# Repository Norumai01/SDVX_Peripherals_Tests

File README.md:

# controller_subtests

Breadboard prototyping tests for a custom Sound Voltex (SDVX) controller built on the Raspberry Pi Pico 2 H (RP2350).

Each subfolder is a self-contained test with its own `CMakeLists.txt` and `main.c`.

---

## Project Structure

```
controller_subtests/
├── CMakeLists.txt          ← top-level, registers all subtests
├── pico_sdk_import.cmake
├── serial_monitor.py       ← Python serial monitor for debugging
├── mx_switch_test/
│   ├── CMakeLists.txt
│   └── main.c              ← Cherry MX Brown button + onboard LED test
└── encoder_test/
    ├── CMakeLists.txt
    └── main.c              ← Bourns PEC11R rotary encoder test
```

---

## Hardware

| Component | Part |
|---|---|
| Microcontroller | Raspberry Pi Pico 2 H (RP2350, pre-soldered headers) |
| Buttons | Cherry MX Brown switches (jumper wires soldered directly to pins) |
| Encoders | Bourns PEC11R-xxxxK (no detents, with push switch) |

---

## Subtest: mx_switch_test

Tests a single Cherry MX Brown switch on GPIO 0. Jumper wires are soldered directly to the two switch pins. Toggles the onboard LED on press/release and prints state over USB serial.

**Wiring:**
```
Switch Pin 1  → GPIO 0  (pin 1)
Switch Pin 2  → GND
```

> **Note:** Uses the Pico's internal pull-up — no external resistor needed. Pin reads HIGH at rest and LOW when pressed.

---

## Subtest: encoder_test

Tests a Bourns PEC11R rotary encoder — quadrature rotation via interrupt and push switch via polling.

**Wiring:**
```
ENC A    → GPIO 10  (pin 14)
ENC C    → GND
ENC B    → GPIO 11  (pin 15)
SW pin 1 → GPIO 12  (pin 16)
SW pin 2 → GND
```

**How it works:**
- An interrupt fires on every rising/falling edge of channel A
- Inside the ISR, A and B are compared — if they differ, direction is CW (+1), if same, direction is CCW (-1)
- The push switch is polled in the main loop with debounce

---

## Building

Requires the [Raspberry Pi Pico SDK](https://github.com/raspberrypi/pico-sdk). Set `PICO_SDK_PATH` in your environment or let CLion handle it via the CMake Environment field.

```bash
mkdir cmake-build-debug && cd cmake-build-debug
cmake ..
make
```

Each subtest outputs its own `.uf2` into its own subfolder:
```
cmake-build-debug/
├── mx_switch_test/
│   └── mx_switch_test.uf2
└── encoder_test/
    └── encoder_test.uf2
```

**To flash:**
1. Hold BOOTSEL on the Pico while plugging in USB
2. It mounts as a drive called `RP2350`
3. Drag and drop the `.uf2` onto the `RP2350` drive

---

## Serial Monitor

Use the included `serial_monitor.py` to watch output over USB serial.

**Requirements:**
```bash
pip install pyserial
```

**Run:**
```bash
python serial_monitor.py
```

Defaults to `COM3` at `115200` baud. Edit `PORT` at the top of the script if your Pico is on a different port (check Device Manager → Ports (COM & LPT)).

## CLion Serial Monitor (alternative)

CLion has a built-in serial monitor under **Tools → Serial Monitor**.

Settings that must be enabled for it to work with the Pico:
- **Enable HW Flow Control** — on
- **Local Echo** — on
- **DTR** — enabled (this is what actually triggers the Pico to send output)

Without DTR enabled, the monitor connects but receives nothing.

---

## Notes

- Both encoder A and B pins use the Pico's internal pull-ups — no external resistors needed for basic testing
- For final PCB design, add a hardware filter (10KΩ + 0.01µF on each channel) per the PEC11R datasheet recommendation to reduce contact bounce at higher RPM
- The encoder's position counter is unbounded (`volatile int`) — for HID use, report the delta each frame rather than an absolute value

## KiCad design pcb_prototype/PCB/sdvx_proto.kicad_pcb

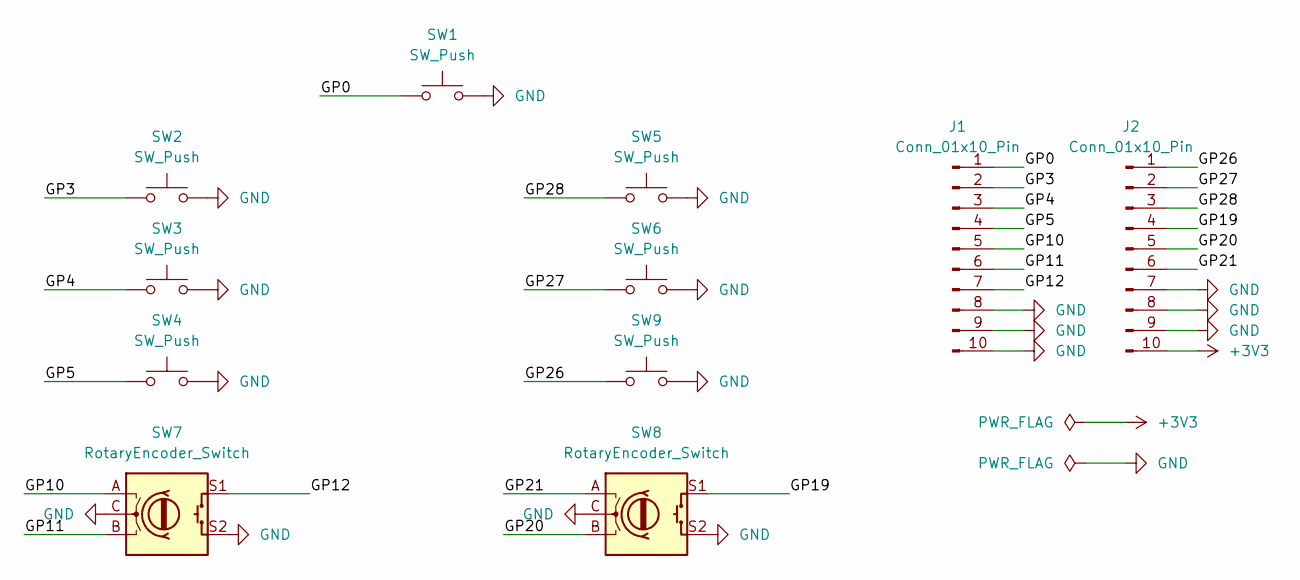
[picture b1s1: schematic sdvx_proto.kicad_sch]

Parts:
J1, J2: Conn_01x10_Pin; PinHeader_1x10_P2.54mm_Vertical
SW1, SW2, SW3, SW4, SW5, SW6, SW9: SW_Push; MX-Solderable-1U
SW7, SW8: RotaryEncoder_Switch; RotaryEncoder_Alps_EC11E-Switch_Vertical_H20mm

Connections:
+3V3: J2.10
/GP0: J1.1, SW1.1
/GP3: J1.2, SW2.1
/GP4: J1.3, SW3.1
/GP5: J1.4, SW4.1
/GP10: J1.5, SW7.A
/GP11: J1.6, SW7.B
/GP12: J1.7, SW7.S1
/GP19: J2.4, SW8.S1
/GP20: J2.5, SW8.B
/GP21: J2.6, SW8.A
/GP26: J2.1, SW9.1
/GP27: J2.2, SW6.1
/GP28: J2.3, SW5.1
GND: J1.8, J1.9, J1.10, J2.7, J2.8, J2.9, SW1.2, SW2.2, SW3.2, SW4.2, SW5.2, SW6.2, SW7.C, SW7.S2, SW8.C, SW8.S2, SW9.2

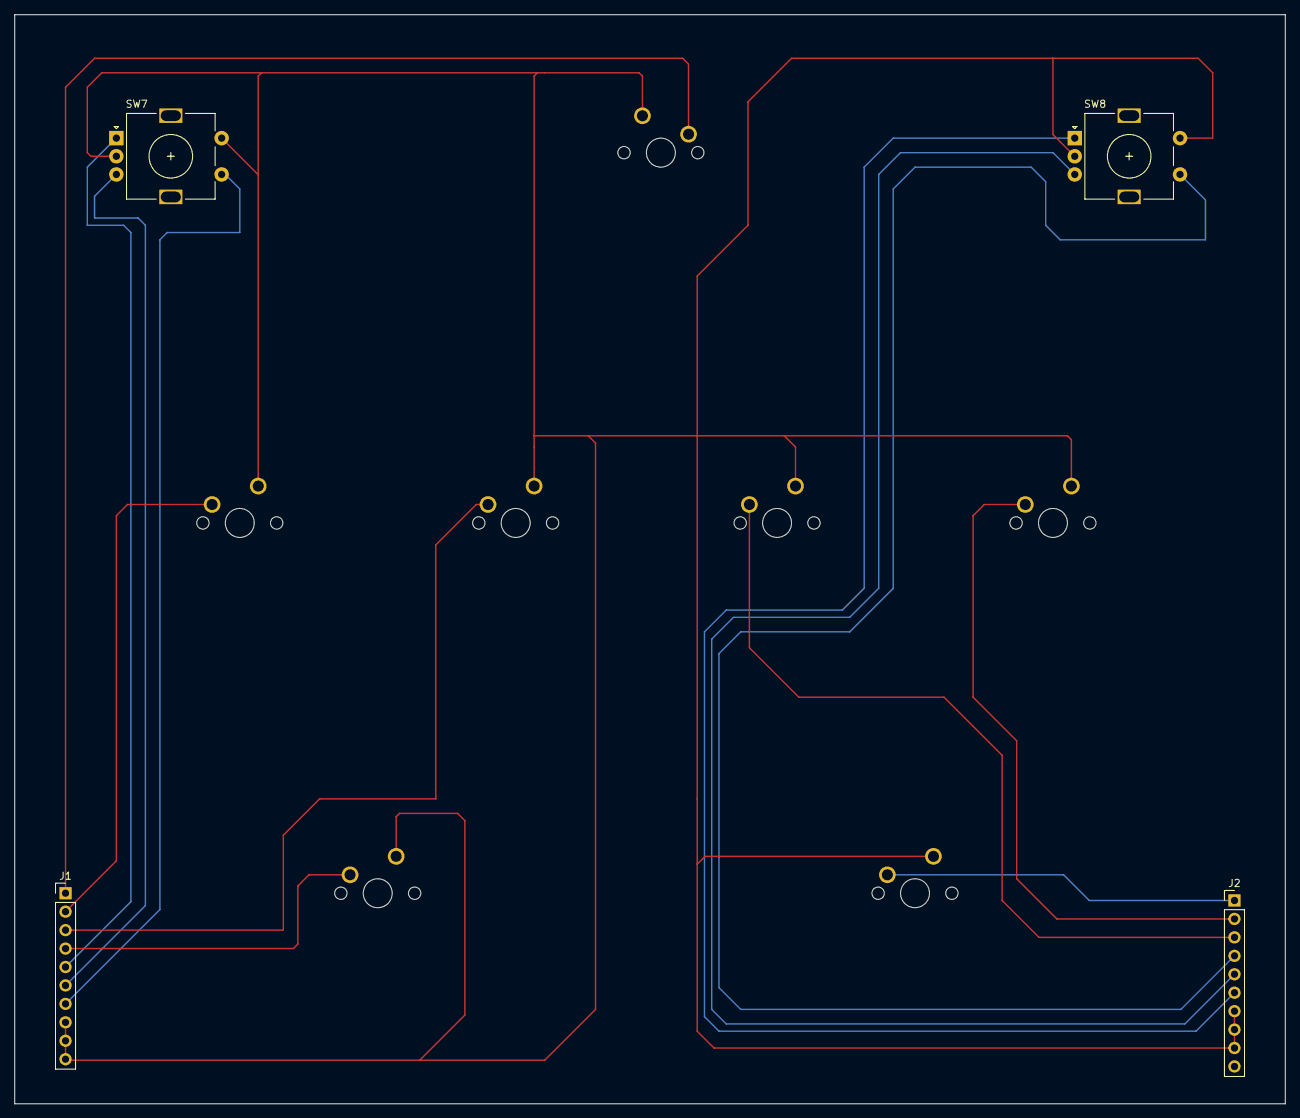
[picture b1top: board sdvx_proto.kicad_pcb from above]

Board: 2 copper layers, 175.0 x 150.0 mm, 11 parts (1 on the bottom side), 14 nets.

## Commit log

2026-03-11 I'm batman. Added peripheal tests for mx keyboard button and rotary encoders.
2026-03-11 Updated SETUP Guide.
2026-03-12 Tested with both button and encoder and implement connection with usb to PC.
2026-03-16 Added PCB prototype and code for testing it.
